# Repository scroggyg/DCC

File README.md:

View this project on [CADLAB.io](https://cadlab.io/project/1665). 

# DCC-
Digital Control project
This will include the DCC Accessory Eagle files and code
Also in future a DCC Controller and code
Based around Teensy 3.5 & 3.6

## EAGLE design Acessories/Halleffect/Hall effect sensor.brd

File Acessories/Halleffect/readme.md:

Eagle files for Hall effect switch

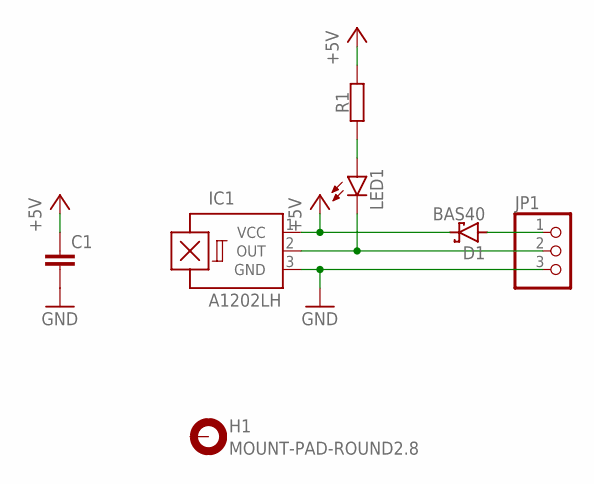
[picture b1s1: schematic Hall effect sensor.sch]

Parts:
C1: C-EUC0805; C0805
D1: BAS40; SOT23
H1: MOUNT-PAD-ROUND2.8; 2,8-PAD
IC1: A1202LH; SOT23-W
JP1: PINHD-1X3; 1X03
LED1: LEDCHIPLED_0603; CHIPLED_0603
R1: RESISTORR0805-3D; R0805

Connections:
+5V: C1.1, D1.3 (C), IC1.1 (VCC), R1.2
GND: C1.2, IC1.3 (GND), JP1.3
unnamed: D1.1 (A), JP1.1
unnamed: IC1.2 (OUT), JP1.2, LED1.C
unnamed: LED1.A, R1.1

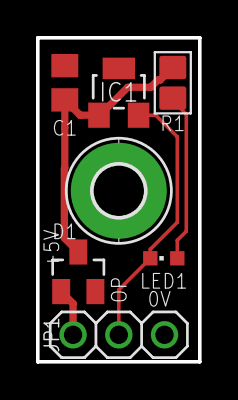
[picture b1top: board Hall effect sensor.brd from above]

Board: 2 copper layers, 9.0 x 18.0 mm, 7 parts (0 on the bottom side), 5 nets.

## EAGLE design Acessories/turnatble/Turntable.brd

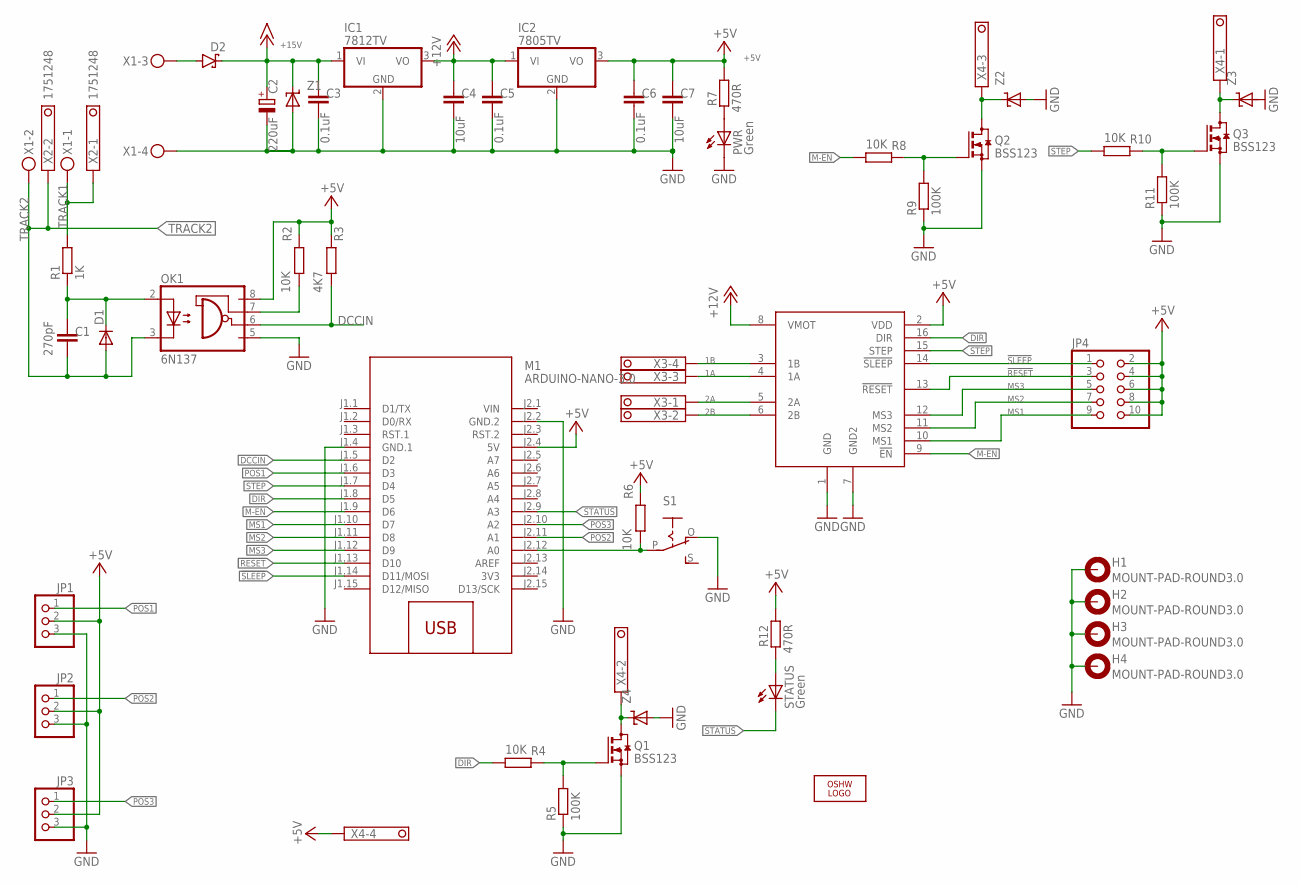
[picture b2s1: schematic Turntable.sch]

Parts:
C1: 270pF; 0805
C2: 220uF; E7,5-16
C3, C5, C6: 0.1uF; 0805
C4, C7: 10uF; 0805
D1: CGRM4002-G; SOD-123_MINI-SMA
D2: SCHOTTKY-DIODESMD; SMB
H1, H2, H3, H4: MOUNT-PAD-ROUND3.0; 3,0-PAD
IC1: 7812TV; TO220V
IC2: 7805TV; TO220V
JP1, JP2, JP3: PINHD-1X3; 1X03
JP4: PINHD-2X5; 2X05
LOGO1: OSHW_LOGO_6MILX0200-NT; OSHW_6X200_NOTEXT
M1: ARDUINO-NANO-3.0
OK1: 6N137; DIL08
PWR: Green; LED3MM
Q1, Q2, Q3: BSS123; SOT23
R1: 1K; R0805
R2, R4, R6, R8, R10: 10K; R0805
R3: 4K7; R0805
R5, R9, R11: 100K; R0805
R7, R12: 470R; R0805
S1: EG1218S; EG1218
STATUS: Green; LED3MM
U1: A4988; POLOLUA4988
X1: MKDSN1,5/4-5,08
X2: 1751248
X3, X4: 1751264
Z1, Z2, Z3, Z4: MSMPX.X; MICROSMP-T

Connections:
1A: U1.4 (1A), X3.3
1B: U1.3 (1B), X3.4
2A: U1.5 (2A), X3.1
2B: U1.6 (2B), X3.2
3V3: M1.J2.14 (3V3)
!RESET: JP4.3, M1.J1.13 (D10), U1.13 (!RESET)
!SLEEP: JP4.1, M1.J1.14 (D11/MOSI), U1.14 (!SLEEP)
+5V: C6.1, C7.1, IC2.3 (VO), JP1.2, JP2.2, JP3.2, JP4.2, JP4.4, JP4.6, JP4.8, JP4.10, M1.J2.4 (5V), OK1.8 (VCC), R2.2, R3.2, R6.2, R7.2, R12.2, U1.2 (VDD), X4.4
+12V: C4.1, C5.1, IC1.3 (VO), IC2.1 (VI), U1.8 (VMOT)
+15V: C2.+, C3.1, D2.C, IC1.1 (VI), Z1.C
DCCIN: M1.J1.5 (D2), OK1.6 (VO), R3.1
DIR: M1.J1.8 (D5), R4.1, U1.16 (DIR)
GND: C2.-, C3.2, C4.2, C5.2, C6.2, C7.2, H1.B3,0, H2.B3,0, H3.B3,0, H4.B3,0, IC1.2 (GND), IC2.2 (GND), JP1.3, JP2.3, JP3.3, M1.J1.4 (GND.1), M1.J2.2 (GND.2), OK1.5 (GND), PWR.K (C), Q1.2 (S), Q2.2 (S), Q3.2 (S), R5.1, R9.1, R11.1, S1.O, U1.1 (GND), U1.7 (GND2), X1.4, Z1.A, Z2.A, Z4.A
LEARN: M1.J2.12 (A0), R6.1, S1.P
M-EN: M1.J1.9 (D6), R8.1, U1.9 (!EN)
MS1: JP4.9, M1.J1.10 (D7), U1.10 (MS1)
MS2: JP4.7, M1.J1.11 (D8), U1.11 (MS2)
MS3: JP4.5, M1.J1.12 (D9), U1.12 (MS3)
unnamed: D2.A, X1.3
unnamed: C1.1, D1.C, OK1.2 (A), R1.1
unnamed: Q3.1 (G), R10.2, R11.2
unnamed: OK1.7 (VE), R2.1
unnamed: Q3.3 (D), X4.1, Z3.C
unnamed: Q1.1 (G), R4.2, R5.2
unnamed: Q1.3 (D), X4.2, Z4.C
unnamed: R12.1, STATUS.A
unnamed: Q2.1 (G), R8.2, R9.2
unnamed: Q2.3 (D), X4.3, Z2.C
unnamed: PWR.A, R7.1
POS1: JP1.1, M1.J1.6 (D3)
POS2: JP2.1, M1.J2.11 (A1)
POS3: JP3.1, M1.J2.10 (A2)
STATUS: M1.J2.9 (A3), STATUS.K (C)
STEP: M1.J1.7 (D4), R10.1, U1.15 (STEP)
TRACK1: R1.2, X1.1, X2.1
TRACK2: C1.2, D1.A, OK1.3 (C), X1.2, X2.2
VIN: M1.J2.1 (VIN)

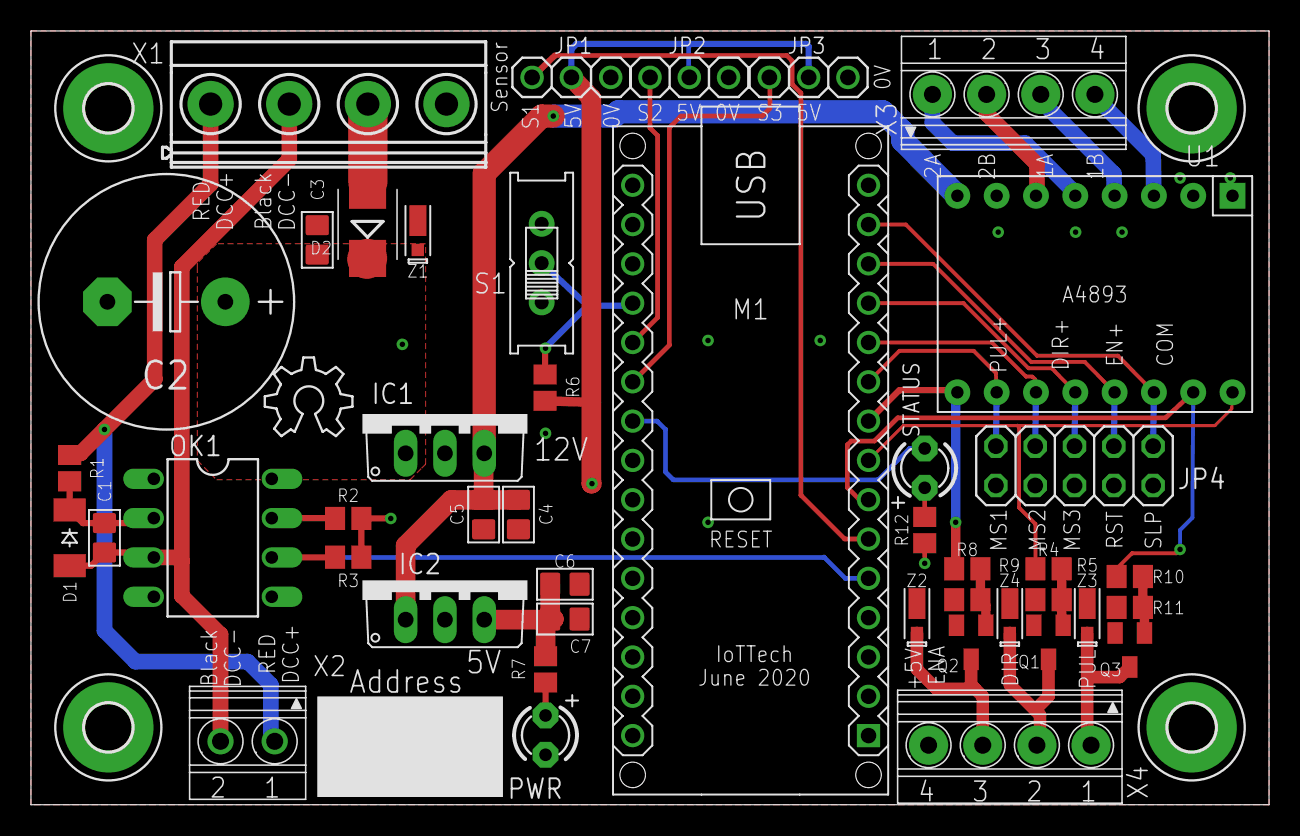
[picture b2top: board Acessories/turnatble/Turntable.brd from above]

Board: 2 copper layers, 80.0 x 50.0 mm, 49 parts (0 on the bottom side), 35 nets.

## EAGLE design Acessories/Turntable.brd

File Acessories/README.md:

Accessories Decoder
Turnouts Board
Created a Mega Turnout controller with built in CDU, 16 outputs, i.e. it can control up t0 8 points/turnouts
Also has 16 darlington outputs over I2C and can sit on Loconet or Xpressnet bus.
Based on Mega1284P
Occupancy board

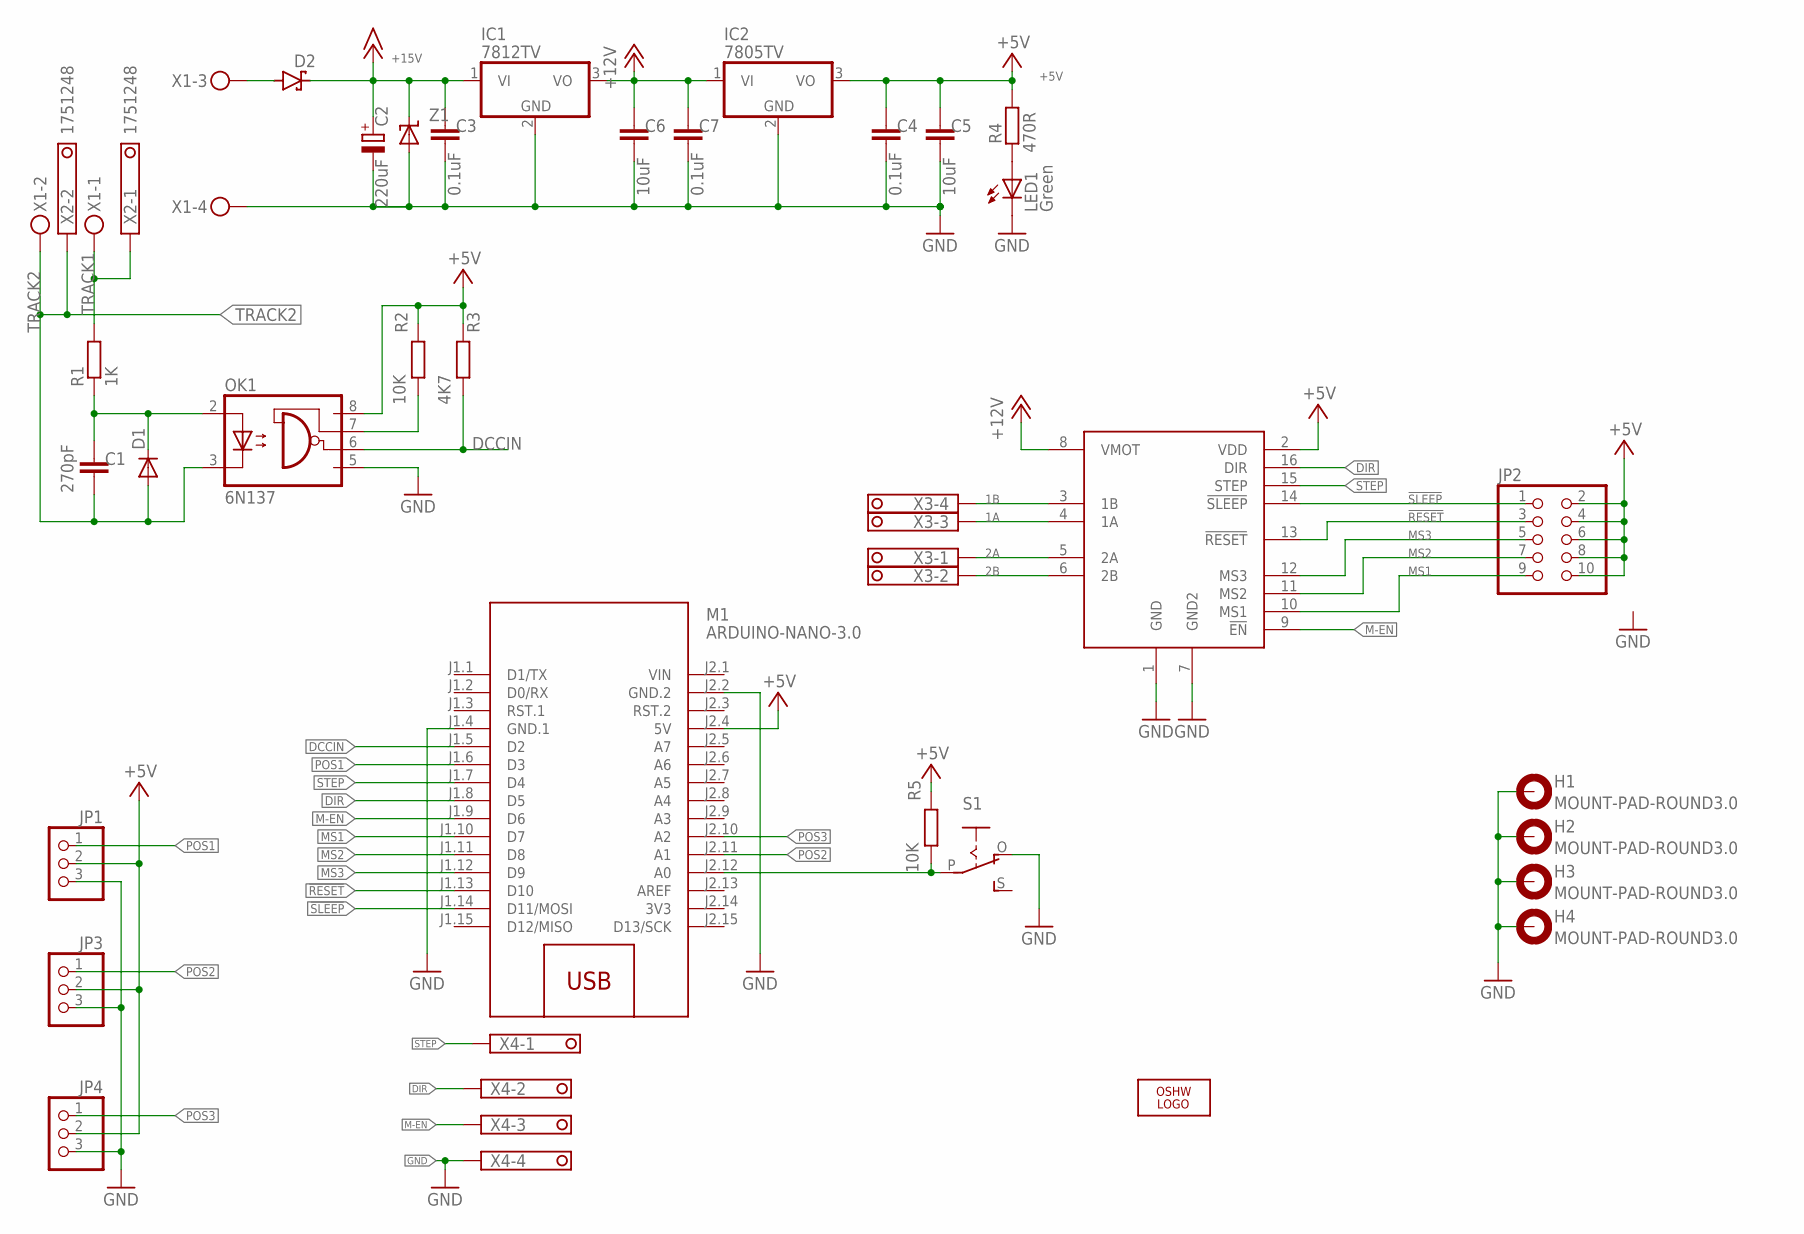
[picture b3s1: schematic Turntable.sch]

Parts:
C1: 270pF; 0805
C2: 220uF; E7,5-16
C3, C4, C7: 0.1uF; 0805
C5, C6: 10uF; 0805
D1: CGRM4002-G; SOD-123_MINI-SMA
D2: SCHOTTKY-DIODESMD; SMB
H1, H2, H3, H4: MOUNT-PAD-ROUND3.0; 3,0-PAD
IC1: 7812TV; TO220V
IC2: 7805TV; TO220V
JP1, JP3, JP4: PINHD-1X3; 1X03
JP2: PINHD-2X5; 2X05
LED1: Green; LED3MM
LOGO1: OSHW_LOGO_6MILX0200-NT; OSHW_6X200_NOTEXT
M1: ARDUINO-NANO-3.0
OK1: 6N137; DIL08
R1: 1K; R0805
R2, R5: 10K; R0805
R3: 4K7; R0805
R4: 470R; R0805
S1: EG1218S; EG1218
U2: A4988; POLOLUA4988
X1: MKDSN1,5/4-5,08
X2: 1751248
X3, X4: 1751264
Z1: TRANSZORB; SMB

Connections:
1A: U2.4 (1A), X3.3
1B: U2.3 (1B), X3.4
2A: U2.5 (2A), X3.1
2B: U2.6 (2B), X3.2
3V3: M1.J2.14 (3V3)
!RESET: JP2.3, M1.J1.13 (D10), U2.13 (!RESET)
!SLEEP: JP2.1, M1.J1.14 (D11/MOSI), U2.14 (!SLEEP)
+5V: C4.1, C5.1, IC2.3 (VO), JP1.2, JP2.2, JP2.4, JP2.6, JP2.8, JP2.10, JP3.2, JP4.2, M1.J2.4 (5V), OK1.8 (VCC), R2.2, R3.2, R4.2, R5.2, U2.2 (VDD)
+12V: C6.1, C7.1, IC1.3 (VO), IC2.1 (VI), U2.8 (VMOT)
+15V: C2.+, C3.1, D2.C, IC1.1 (VI), Z1.1 (C)
DCCIN: M1.J1.5 (D2), OK1.6 (VO), R3.1
DIR: M1.J1.8 (D5), U2.16 (DIR), X4.2
GND: C2.-, C3.2, C4.2, C5.2, C6.2, C7.2, H1.B3,0, H2.B3,0, H3.B3,0, H4.B3,0, IC1.2 (GND), IC2.2 (GND), JP1.3, JP3.3, JP4.3, LED1.K (C), M1.J1.4 (GND.1), M1.J2.2 (GND.2), OK1.5 (GND), S1.O, U2.1 (GND), U2.7 (GND2), X1.4, X4.4, Z1.2 (A)
LEARN: M1.J2.12 (A0), R5.1, S1.P
M-EN: M1.J1.9 (D6), U2.9 (!EN), X4.3
MS1: JP2.9, M1.J1.10 (D7), U2.10 (MS1)
MS2: JP2.7, M1.J1.11 (D8), U2.11 (MS2)
MS3: JP2.5, M1.J1.12 (D9), U2.12 (MS3)
unnamed: D2.A, X1.3
unnamed: C1.1, D1.C, OK1.2 (A), R1.1
unnamed: OK1.7 (VE), R2.1
unnamed: LED1.A, R4.1
POS1: JP1.1, M1.J1.6 (D3)
POS2: JP3.1, M1.J2.11 (A1)
POS3: JP4.1, M1.J2.10 (A2)
STEP: M1.J1.7 (D4), U2.15 (STEP), X4.1
TRACK1: R1.2, X1.1, X2.1
TRACK2: C1.2, D1.A, OK1.3 (C), X1.2, X2.2
VIN: M1.J2.1 (VIN)

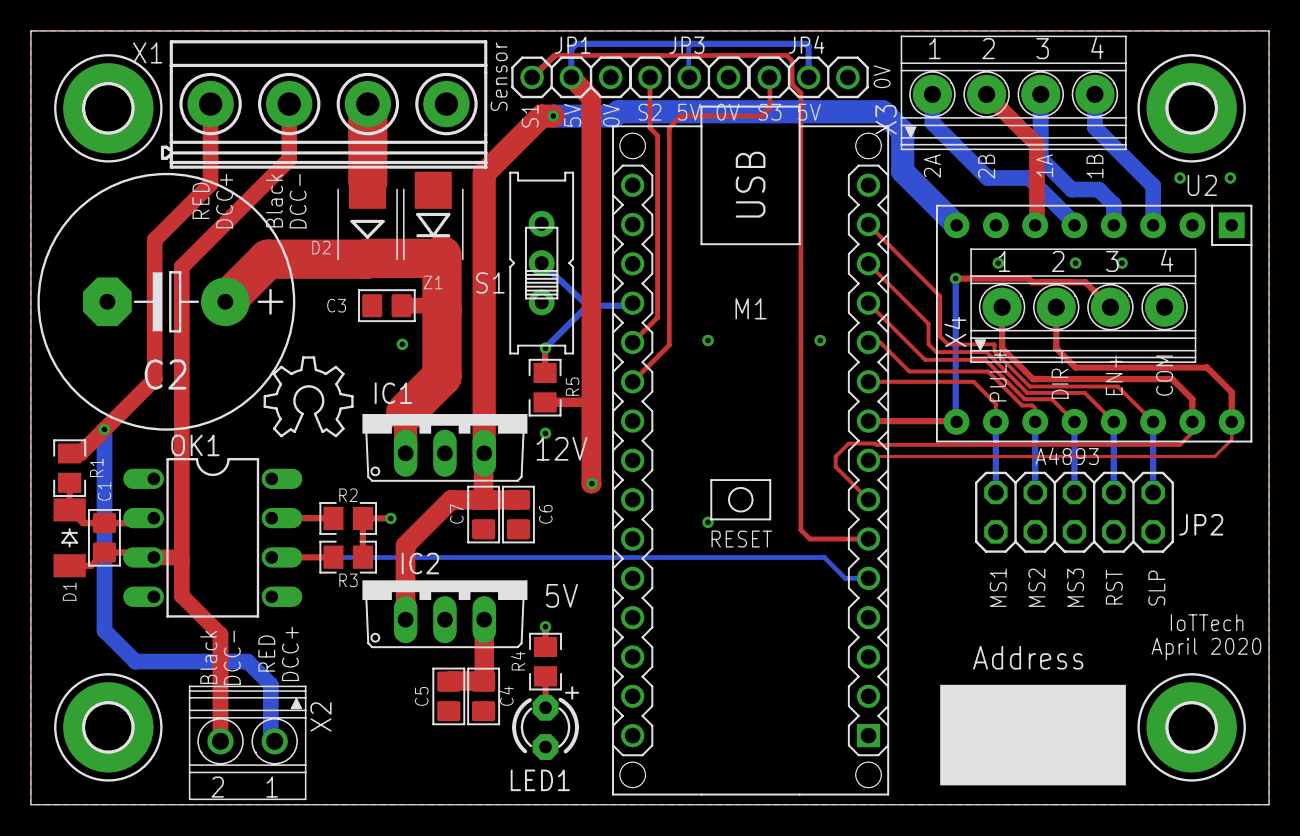
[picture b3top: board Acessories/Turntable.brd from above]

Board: 2 copper layers, 80.0 x 50.0 mm, 35 parts (0 on the bottom side), 27 nets.

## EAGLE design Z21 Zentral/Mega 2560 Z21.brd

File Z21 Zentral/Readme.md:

ATMega2560 Based central Controller
Based on Philip Ghatow design and software
Gerber files for Allpcb.com

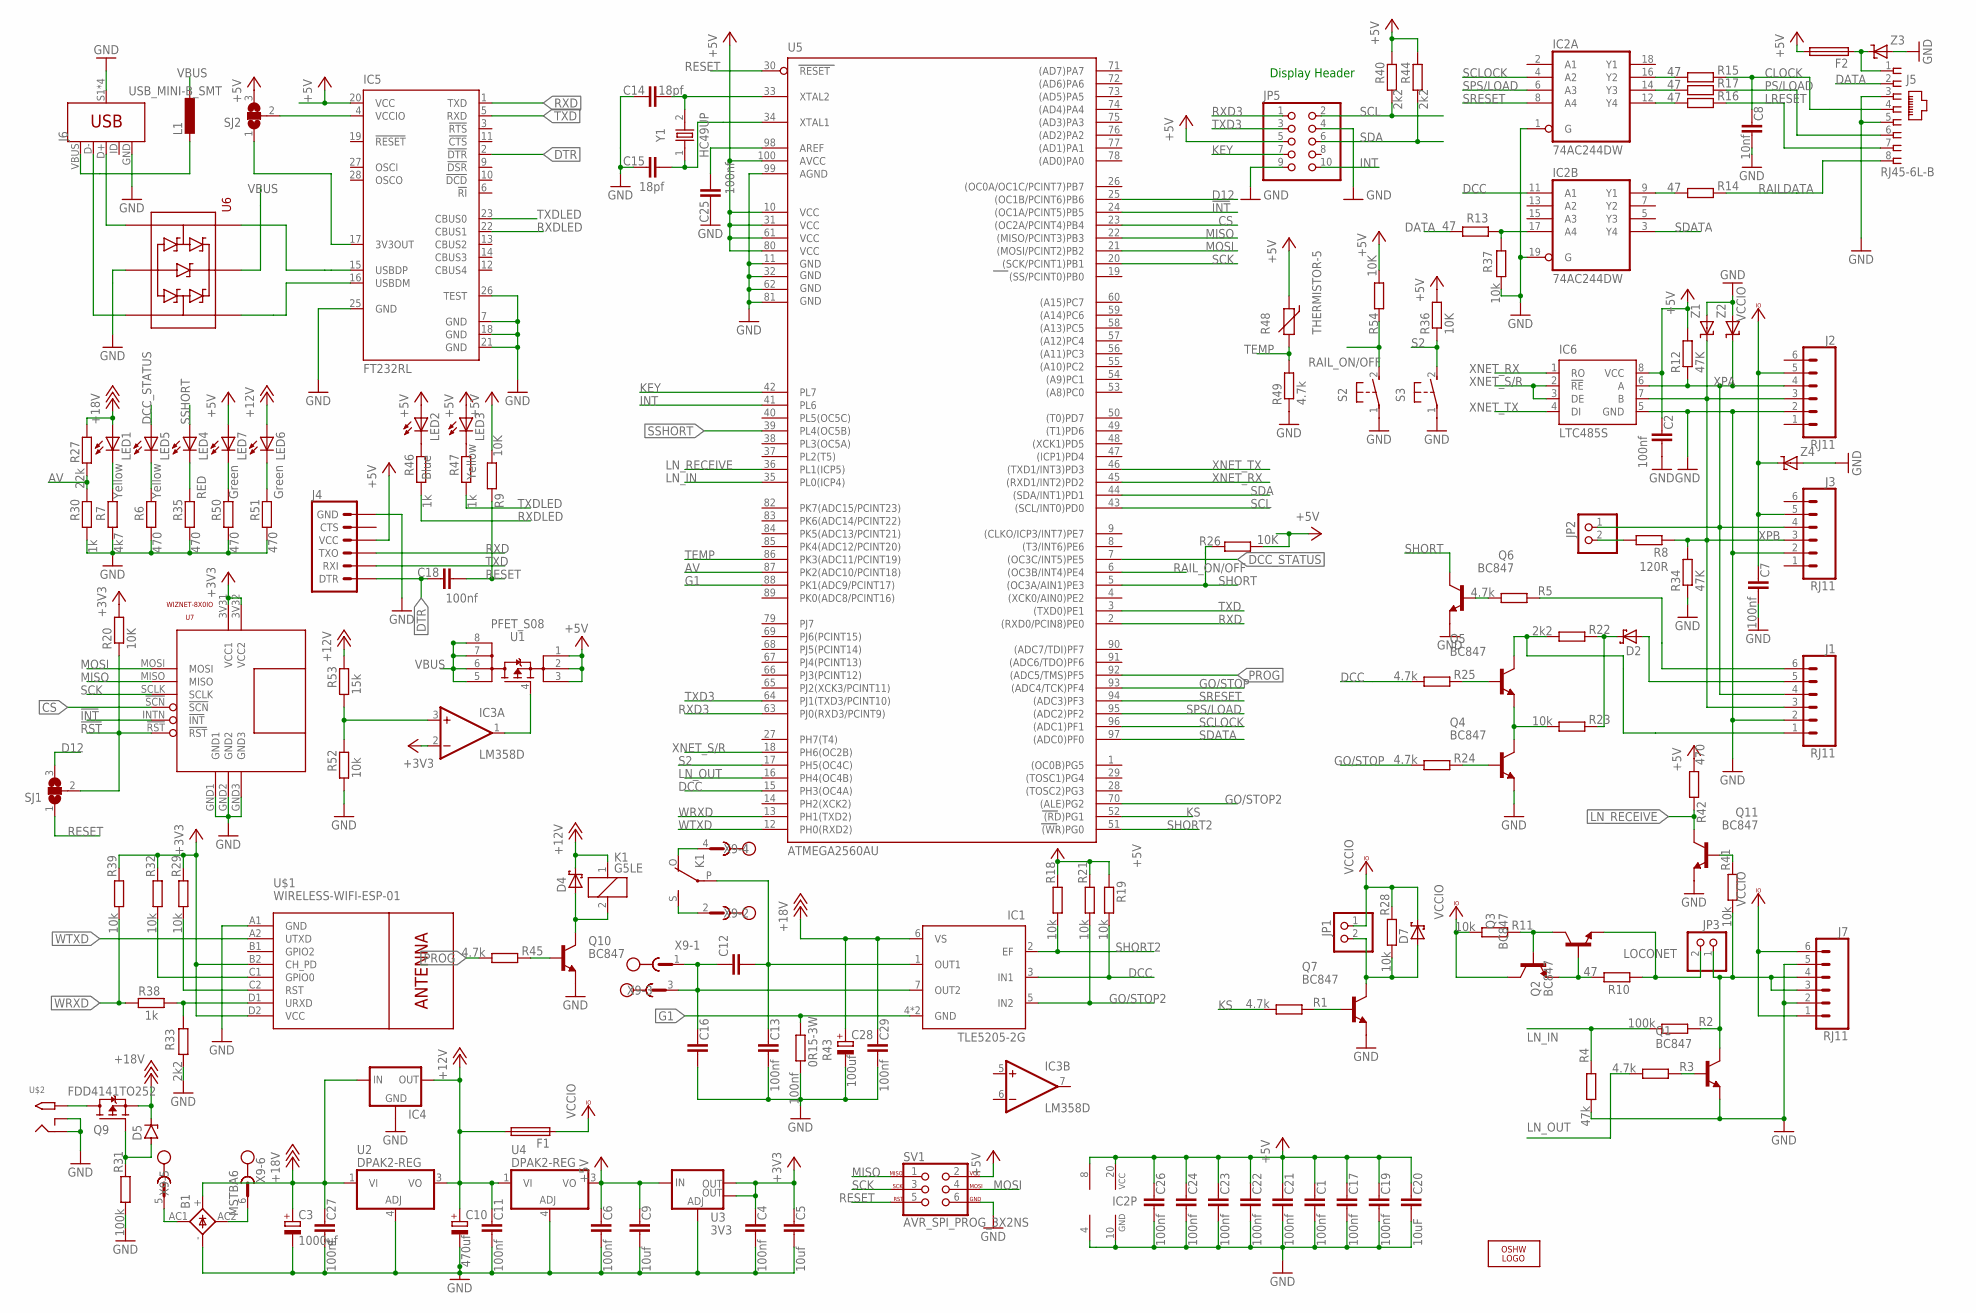
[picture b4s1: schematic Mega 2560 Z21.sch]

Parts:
B1: BRIDGE_RECTIFIER_6AMP; KBU-6D
C1, C2, C4, C6, C7, C11, C17, C18, C19, C21, C22, C23, C24, C25, C26: 100nf; C0603
C3: 1000uf; E5-13
C5, C9: 10uf; C0805
C8: 10nf; C0603
C10: 470uf; E5-13
C12: C-EUC1812; C1812
C13, C16, C29: 100nf; C1206
C14, C15: 18pf; C0603
C20: 10uF; C0805
C27: 100nf; C0805
C28: 100uf; E2-5
D2, D4, D7: MICROSMD-SCHOTTKY-DIODE; MICROSMP
D5: ZENER-DIODESOT23; SOT23
F1, F2: TE5
IC1: TLE5205-2G; P-TO263-7-1
IC2: 74AC244DW; SO20W
IC3: LM358D; SO08
IC4: 78XXS
IC5: FT232RL; SSOP28
IC6: LTC485S; SOIC8
J1, J2, J3, J7: RJ11; RJ11-6
J4: 6_PIN_SERIAL_TARGET; 1X06
J5: RJ45-6L-B; RJ45-NO-SHIELD
J6: USB_MINI-B_SMT; USB-MINIB
JP1, JP2, JP3: PINHD-1X2; 1X02
JP5: PINHD-2X5; 2X05
K1: G5LE
L1: L-EUL2012C; L2012C
LED1, LED3, LED5: Yellow; LED3MM
LED2: Blue; LED3MM
LED4: RED; LED3MM
LED6, LED7: Green; LED3MM
LOGO1: OSHW_LOGO_6MILX0200-NT; OSHW_6X200_NOTEXT
Q1, Q2, Q3, Q4, Q5, Q6, Q7, Q10, Q11: BC847; SOT23
Q9: FDD4141TO252; TO252
R1, R3, R5, R24, R25, R45, R49: 4.7k; R0603
R2, R31: 100k; R0603
R4: 47k; R0603
R6, R35, R42, R50, R51: 470; R0603
R7: 4k7; R0603
R8: 120R; R0603
R9, R20, R26, R36, R54: 10K; R0603
R10, R13, R14, R15, R16, R17: 47; R0603
R11, R18, R19, R21, R23, R28, R29, R32, R37, R39, R41, R52: 10k; R0603
R12, R34: 47K; R0603
R22, R33, R40, R44: 2k2; R0603
R27: 22k; R0603
R30, R38, R46, R47: 1k; R0603
R43: 0R15-3W; P0817V
R48: THERMISTOR-5; R-5
R53: 15k; R0603
S2, S3: 31-XX; B3F-31XX
SJ1, SJ2: SJ2W; SJ_2
SV1: AVR_SPI_PROG_3X2NS; 2X3-NS
U1: PFET_S08; SO08
U2, U4: DPAK2-REG; DPAK2
U3: 3V3; SOT223
U5: ATMEGA2560AU; TQFP100
U6: UABLC6-2SOT23-6L; SOT95P280X145-6N
U7: WIZNET-8X0IO; WIZ850IO
U$1: WIRELESS-WIFI-ESP-01
U$2: 2.1MMJACKTHM; PJ-102A
X9: MSTBA6
Y1: HC49UP
Z1, Z2, Z3, Z4: TRANSZORB-SMA; SMA

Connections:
!INT: U5.24 ((OC1A/PCINT5)PB5), U7.INTN (!INT)
!RST: R20.1, SJ1.2, U7.!RST
+3V3: C4.1, C5.1, IC3.2 (-IN), R20.2, R29.1, R32.1, R39.1, U3.2 (OUT), U3.4 (OUT), U7.3V31 (VCC1), U7.3V32 (VCC2), U$1.B2 (CH_PD), U$1.D2 (VCC)
+5V: C1.1, C2.1, C6.1, C9.1, C17.1, C19.1, C20.1, C21.1, C22.1, C23.1, C24.1, C26.1, F2.2, IC2.20 (VCC), IC3.8 (V+), IC5.20 (VCC), IC6.8 (VCC), J4.4 (VCC), JP5.5, LED2.A, LED3.A, LED7.A, R9.2, R12.2, R18.1, R19.1, R21.1, R26.2, R36.2, R40.2, R42.2, R44.2, R48.1, R54.2, SJ2.3, SV1.2, U1.1 (S1), U1.2 (S2), U1.3 (S3), U3.3 (IN), U4.3 (VO), U5.10 (VCC), U5.31 (VCC1), U5.61 (VCC2), U5.80 (VCC3), U5.100 (AVCC)
+12V: C10.+, C11.1, D4.C, F1.2, IC4.OUT, K1.1, LED6.A, R53.2, U2.3 (VO), U4.1 (VI)
+18V: B1.+, C3.+, C27.1, C28.+, C29.1, D5.3 (C), IC1.6 (VS), IC4.IN, LED1.A, Q9.2 (S), R27.2, U2.1 (VI)
AV: R27.1, R30.2, U5.87 (PK2(ADC10/PCINT18))
CLOCK: C8.1, J5.4, R15.1
CS: U5.23 ((OC2A/PCINT4)PB4), U7.!SCN
D12: SJ1.3, U5.25 ((OC1B/PCINT6)PB6)
DATA: J5.2, R13.2
DCC: IC1.3 (IN1), IC2.11 (A1), R19.2, R25.2, U5.15 (PH3(OC4A))
DCC_STATUS: LED5.A, U5.7 ((OC3C/INT5)PE5)
DTR: C18.1, IC5.2 (!DTR), J4.1 (DTR)
G1: IC1.4 (GND), IC1.8 (GND), R43.2, U5.88 (PK1(ADC9/PCINT17))
GND: B1.-, C1.2, C2.2, C3.-, C4.2, C5.2, C6.2, C7.2, C8.2, C9.2, C10.-, C11.2, C13.2, C14.1, C15.1, C16.2, C17.2, C19.2, C20.2, C21.2, C22.2, C23.2, C24.2, C25.1, C26.2, C27.2, C28.-, C29.2, IC2.1 (G), IC2.10 (GND), IC2.19 (G), IC3.4 (V-), IC4.GND, IC5.7 (GND), IC5.18 (GND), IC5.21 (GND), IC5.25 (GND), IC5.26 (TEST), IC6.5 (GND), J1.2, J2.2, J3.2, J4.6 (GND), J5.3, J5.5, J6.GND, J6.S1 (SHIELD), J6.S2 (SHIELD), J6.S3 (SHIELD), J6.S4 (SHIELD), J7.2, J7.5, JP5.4, JP5.9, Q1.2 (E), Q4.2 (E), Q6.2 (E), Q7.2 (E), Q10.2 (E), Q11.2 (E), R4.2, R6.1, R7.1, R30.1, R31.2, R33.2, R34.1, R35.1, R37.2, R43.1, R49.1, R50.1, R51.1, R52.1, S2.1, S3.1, SV1.6, U2.4 (ADJ), U3.1 (ADJ), U4.4 (ADJ), U5.11 (GND), U5.32 (GND1), U5.62 (GND2), U5.81 (GND3), U5.99 (AGND), U6.2 (GND), U7.GND1, U7.GND2, U7.GND3, U$1.A1 (GND), U$2.RING, U$2.RING_SW, Z1.A, Z2.A, Z3.A, Z4.A
GO/STOP: R24.2, U5.93 ((ADC4/TCK)PF4)
GO/STOP2: IC1.5 (IN2), R21.2, U5.70 ((ALE)PG2)
INT: JP5.10, U5.41 (PL6)
KEY: JP5.7, U5.42 (PL7)
KS: R1.2, U5.52 ((RD)PG1)
LN_IN: R2.2, R4.1, U5.35 (PL0(ICP4))
LN_OUT: R3.2, U5.16 (PH4(OC4B))
LN_RECEIVE: Q11.3 (C), R42.1, U5.36 (PL1(ICP5))
LOCONET: JP3.2, Q2.2 (E), R10.1
LRESET: J5.7, R16.1
MISO: SV1.1, U5.22 ((MISO/PCINT3)PB3), U7.MISO
MOSI: SV1.4, U5.21 ((MOSI/PCINT2)PB2), U7.MOSI
unnamed: LED5.K (C), R6.2
unnamed: C25.2, U5.98 (AREF)
unnamed: LED4.K (C), R35.2
unnamed: IC2.16 (Y2), R15.2
unnamed: Q2.3 (C), Q3.1 (B), R11.1
unnamed: Q1.1 (B), R3.1
unnamed: D7.A, JP1.2, Q7.3 (C), R28.2
unnamed: Q2.1 (B), Q3.2 (E), R10.2
unnamed: IC2.17 (A4), R13.1, R37.1
unnamed: IC2.14 (Y3), R17.2
unnamed: IC2.12 (Y4), R16.2
unnamed: Q7.1 (B), R1.1
unnamed: IC2.9 (Y1), R14.2
unnamed: Q5.1 (B), R25.1
unnamed: Q4.1 (B), R24.1
unnamed: Q4.3 (C), Q5.2 (E), R23.2
unnamed: D2.A, J1.5
unnamed: D2.C, R22.1, R23.1
unnamed: J1.1, Q5.3 (C), R22.2
unnamed: Q6.1 (B), R5.2
unnamed: J1.6, R5.1
unnamed: D5.1 (A), Q9.1 (G), R31.1
unnamed: Q9.3 (D), U$2.TIP
unnamed: C14.2, U5.33 (XTAL2), Y1.2
unnamed: C12.2, C13.1, IC1.1 (OUT1), K1.P
unnamed: C12.1, C16.1, IC1.7 (OUT2), X9.1, X9.3
unnamed: F2.1, J5.1, Z3.C
unnamed: C15.2, U5.34 (XTAL1), Y1.1
unnamed: LED1.K (C), R7.2
unnamed: R32.2, U$1.C1 (GPIO0)
unnamed: R29.2, U$1.C2 (RST)
unnamed: K1.S, X9.2
unnamed: JP2.2, R8.2
unnamed: B1.AC2, X9.6
unnamed: R33.1, R38.2, U$1.D1 (URXD)
unnamed: J6.D+, U6.3 (IO2I)
unnamed: K1.O, X9.4
unnamed: J6.D-, U6.1 (IO1I)
unnamed: D4.A, K1.2, Q10.3 (C)
unnamed: B1.AC1, X9.5
unnamed: LED7.K (C), R50.2
unnamed: Q10.1 (B), R45.1
unnamed: J7.3, J7.4, JP3.1, Q1.3 (C), R2.1, R41.2
unnamed: Q11.1 (B), R41.1
unnamed: IC5.15 (USBDP), U6.4 (IO2O)
unnamed: LED2.K (C), R46.2
unnamed: LED3.K (C), R47.2
unnamed: IC5.16 (USBDM), U6.6 (IO1O)
unnamed: J6.VBUS, L1.2
unnamed: LED6.K (C), R51.2
unnamed: IC5.4 (VCCIO), SJ2.2
unnamed: IC5.17 (3V3OUT), SJ2.1
unnamed: IC3.1 (OUT), U1.4 (G)
unnamed: IC3.3 (+IN), R52.2, R53.1
PROG: R45.2, U5.92 ((ADC5/TMS)PF5)
PS/LOAD: J5.6, R17.1
RAILDATA: J5.8, R14.1
RAIL_ON/OFF: R54.1, S2.2 (S), U5.6 ((OC3B/INT4)PE4)
RESET: C18.2, R9.1, SJ1.1, SV1.5, U5.30 (RESET)
RXD: IC5.1 (TXD), J4.3 (TXO), U5.2 ((RXD0/PCIN8)PE0)
RXD3: JP5.1, U5.63 (PJ0(RXD3/PCINT9))
RXDLED: IC5.22 (CBUS1), R46.1
S2: R36.1, S3.2 (S), U5.17 (PH5(OC4C))
SCK: SV1.3, U5.20 ((SCK/PCINT1)PB1), U7.SCLK
SCL: JP5.2, R40.1, U5.43 ((SCL/INT0)PD0)
SCLOCK: IC2.4 (A2), U5.96 ((ADC1)PF1)
SDA: JP5.6, R44.1, U5.44 ((SDA/INT1)PD1)
SDATA: IC2.3 (Y4), U5.97 ((ADC0)PF0)
SHORT: Q6.3 (C), R26.1, U5.5 ((OC3A/AIN1)PE3)
SHORT2: IC1.2 (EF), R18.2, U5.51 ((WR)PG0)
SPS/LOAD: IC2.6 (A3), U5.95 ((ADC2)PF2)
SRESET: IC2.8 (A4), U5.94 ((ADC3)PF3)
SSHORT: LED4.A, U5.39 (PL4(OC5B))
TEMP: R48.2, R49.2, U5.86 (PK3(ADC11/PCINT19))
TXD: IC5.5 (RXD), J4.2 (RXI), U5.3 ((TXD0)PE1)
TXD3: JP5.3, U5.64 (PJ1(TXD3/PCINT10))
TXDLED: IC5.23 (CBUS0), R47.1
VBUS: L1.1, U1.5 (D4), U1.6 (D3), U1.7 (D2), U1.8 (D1), U6.5 (VDD)
VCCIO: C7.1, D7.C, F1.1, J2.5, J3.5, J7.1, J7.6, JP1.1, Q3.3 (C), R11.2, R28.1, Z4.C
WRXD: R38.1, R39.2, U5.13 (PH1(TXD2))
WTXD: U5.12 (PH0(RXD2)), U$1.A2 (UTXD)
XNET_RX: IC6.1 (RO), U5.45 ((RXD1/INT2)PD2)
XNET_S/R: IC6.2 (!RE), IC6.3 (DE), U5.18 (PH6(OC2B))
XNET_TX: IC6.4 (DI), U5.46 ((TXD1/INT3)PD3)
XPA: IC6.6 (A), J1.4, J2.4, J3.4, JP2.1, R12.1, Z2.C
XPB: IC6.7 (B), J1.3, J2.3, J3.3, R8.1, R34.2, Z1.C

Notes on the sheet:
Display Header

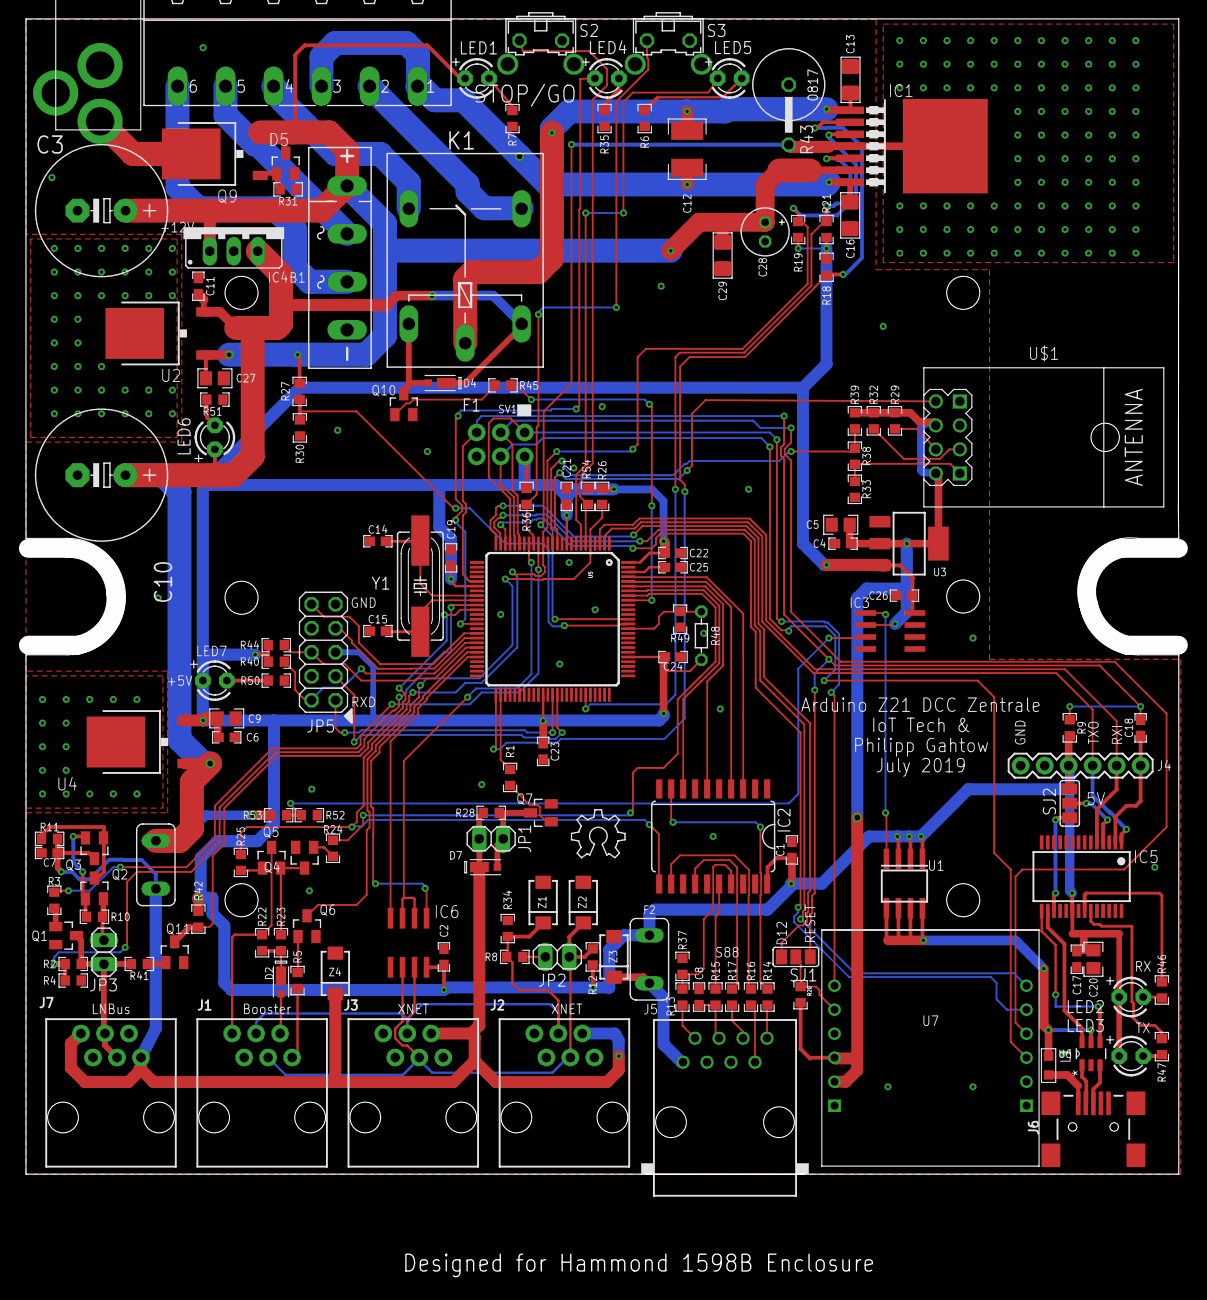
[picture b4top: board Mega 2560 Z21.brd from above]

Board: 2 copper layers, 122.0 x 122.3 mm, 147 parts (0 on the bottom side), 114 nets.

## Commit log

2018-04-27 Add files via upload
    First pcb revision
2018-05-01 Create Accessories
2019-04-01 Backlink to CADLAB.io has been added.
2019-04-30 Add files via upload
    Added learn switch, modified the CDU and 2 x 8 distribution strip for DCC to sections
2019-05-16 Add files via upload
    Added Turntable board based on Nano
    Added learn switch to Turnouts board, moved parts to allow for DC/DC modules
2019-05-16 Add files via upload
    Added 12V regulator, Address label
2019-05-17 Add files via upload
    Minor tweaks
2019-05-21 Add files via upload
    Added 3d files for the turntable bracket, and build instructions
2019-05-24 Add files via upload
    Added GPIO control of the stepper motor board settings, updated Peco turntable build instructions.
2019-07-10 Add files via upload
    added additional power distribution options
2019-07-10 Add files via upload
    Updated turntable design, added 3.5mm connector for stepper motor and direct control of the stepping levels
2019-07-27 Add files via upload
    NMRA Accessory decoder
    Added kludge to address to with Roco (+4 to all addresses)
    Added status light to show that board is running
    Began to add support for Learning mode
    Began to add support for storing CVs in EEPROM
2019-07-29 Add files via upload
    Changed 6 way power connector to allow connector to fit
    Added PFET on input instead of Diode
    Tidied up PCB Legends
2019-07-31 Add files via upload
    Added P Channel FET, replacing Diode
2019-07-31 Add files via upload
    Added SPI header for programming
2019-07-31 Add files via upload
    Changed Diodes on Turnouts board to SMP
2019-08-19 Add files via upload
    added 2 more sensor inputs to enable multiple sensing locations. Intended home, first engine, last engine
2020-04-16 Changed power connector and minor moves of components
2020-04-20 Added connector for external stepper drive
2020-06-13 Turntable control board
    Added support for external microstepper driver
2024-09-08 Create readme.md
    Created folder
2024-09-08 Initial commit of files

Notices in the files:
parts and their libraries:
SparkFun-IC-Power: Licensing: Creative Commons ShareAlike 4.0 International - https://creativecommons.org/licenses/by-sa/4.0
diy-modules: Released under the Creative Commons Attribution 4.0 International License: http://creativecommons.org/licenses/by/4.0
